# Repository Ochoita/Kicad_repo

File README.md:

# Kicad_repo
Mis proyectos de Kicad V7, perdón, ahora seran V8 espero pipipieppepe

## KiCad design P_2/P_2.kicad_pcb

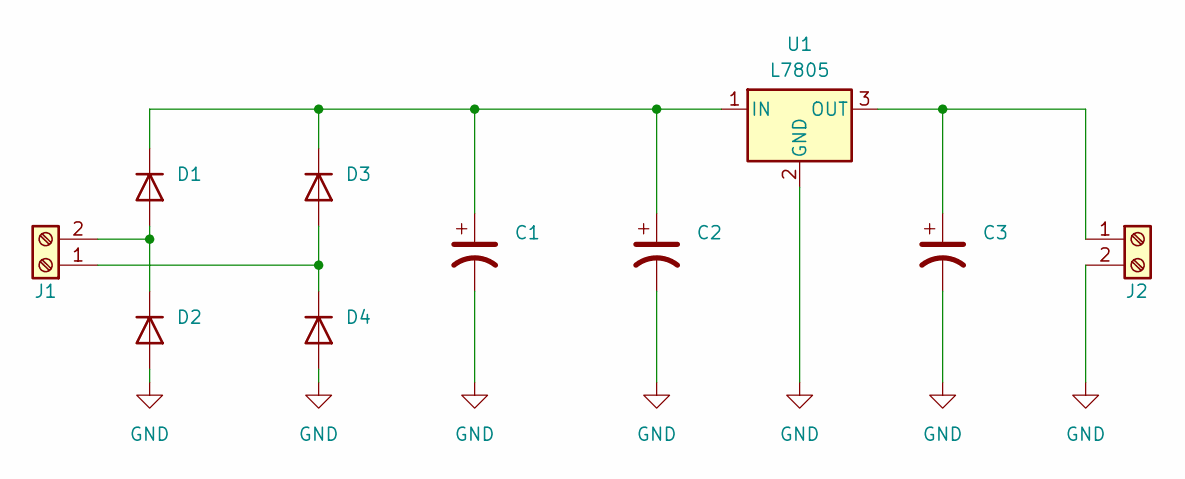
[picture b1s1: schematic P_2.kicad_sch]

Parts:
C1: C_Polarized_US; CP_Radial_D10.0mm_P5.00mm
C2, C3: C_Polarized_US; CP_Radial_D5.0mm_P2.00mm
D1, D2, D3, D4: 1N4004; D_DO-41_SOD81_P10.16mm_Horizontal
J1, J2: Screw_Terminal_01x02; TerminalBlock_bornier-2_P5.08mm
U1: L7805; TO-220-3_Vertical

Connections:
GND: C1.2, C2.2, C3.2, D2.2 (A), D4.2 (A), J2.2, U1.2 (GND)
unnamed 1: D1.2 (A), D2.1 (K), J1.2; also elsewhere on the board
unnamed: C1.1, C2.1, D1.1 (K), D3.1 (K), U1.1 (IN)
unnamed 3: D3.2 (A), D4.1 (K), J1.1; also elsewhere on the board
unnamed: C3.1, J2.1, U1.3 (OUT)

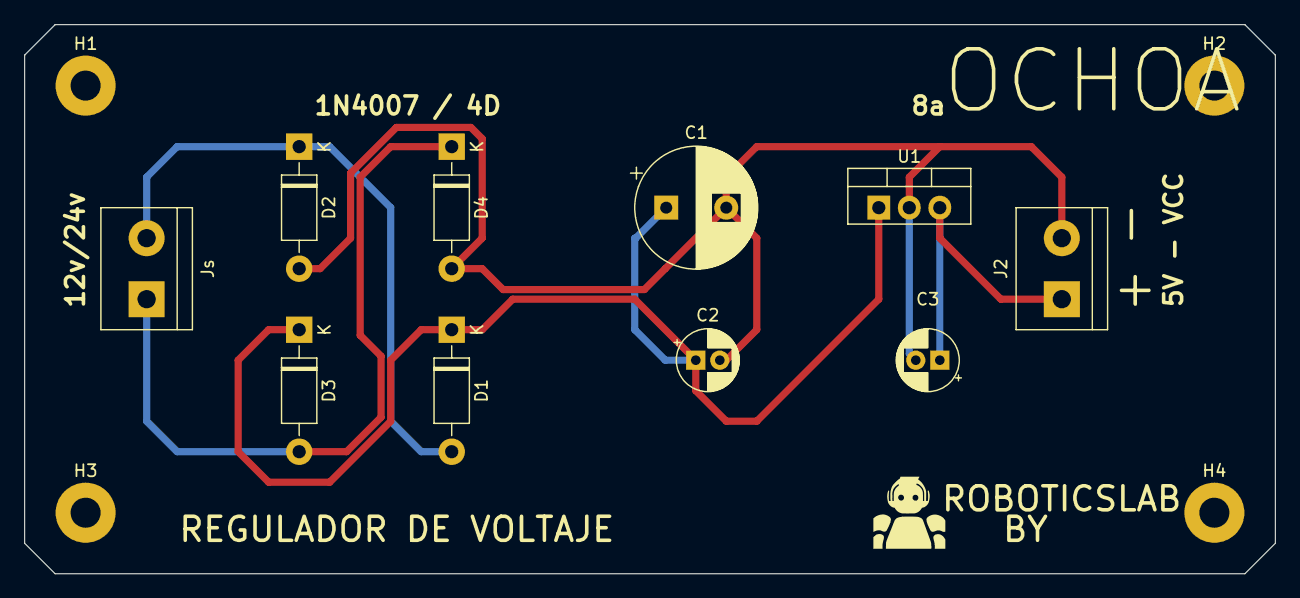
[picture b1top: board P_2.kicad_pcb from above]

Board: 2 copper layers, 104.1 x 45.7 mm, 14 parts (0 on the bottom side), 5 nets.

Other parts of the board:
H1, H2, H3, H4: MountingHole_2.5mm_Pad
Js: Screw_Terminal_01x02; TerminalBlock_bornier-2_P5.08mm

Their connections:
unnamed 1: Js.2; also elsewhere on the board
unnamed 3: Js.1; also elsewhere on the board

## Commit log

2024-12-17 Todo para subirlo a GH
2024-12-18 Cambio con SSH
2024-12-18 Ultimo comitt
2024-12-18 Ahora sí el ultimo
2024-12-18 Prueba con SSH
2024-12-18 Ahora sí
2024-12-18 Ahora si
2024-12-18 Ahora si porfa
2024-12-18 Espermos que sí
2024-12-18 Somos ahora sí
2024-12-18 Una versión de mi webada
2024-12-18 Committt pliss
2024-12-18 Ahora
2024-12-18 Ahora sís
2024-12-18 Ahora peeee
2024-12-18 Es la verdadera
